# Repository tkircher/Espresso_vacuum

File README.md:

# Espresso vacuum
Released under the Permissive version of the Cern Open Hardware License v2 (CERN-OHL-P)

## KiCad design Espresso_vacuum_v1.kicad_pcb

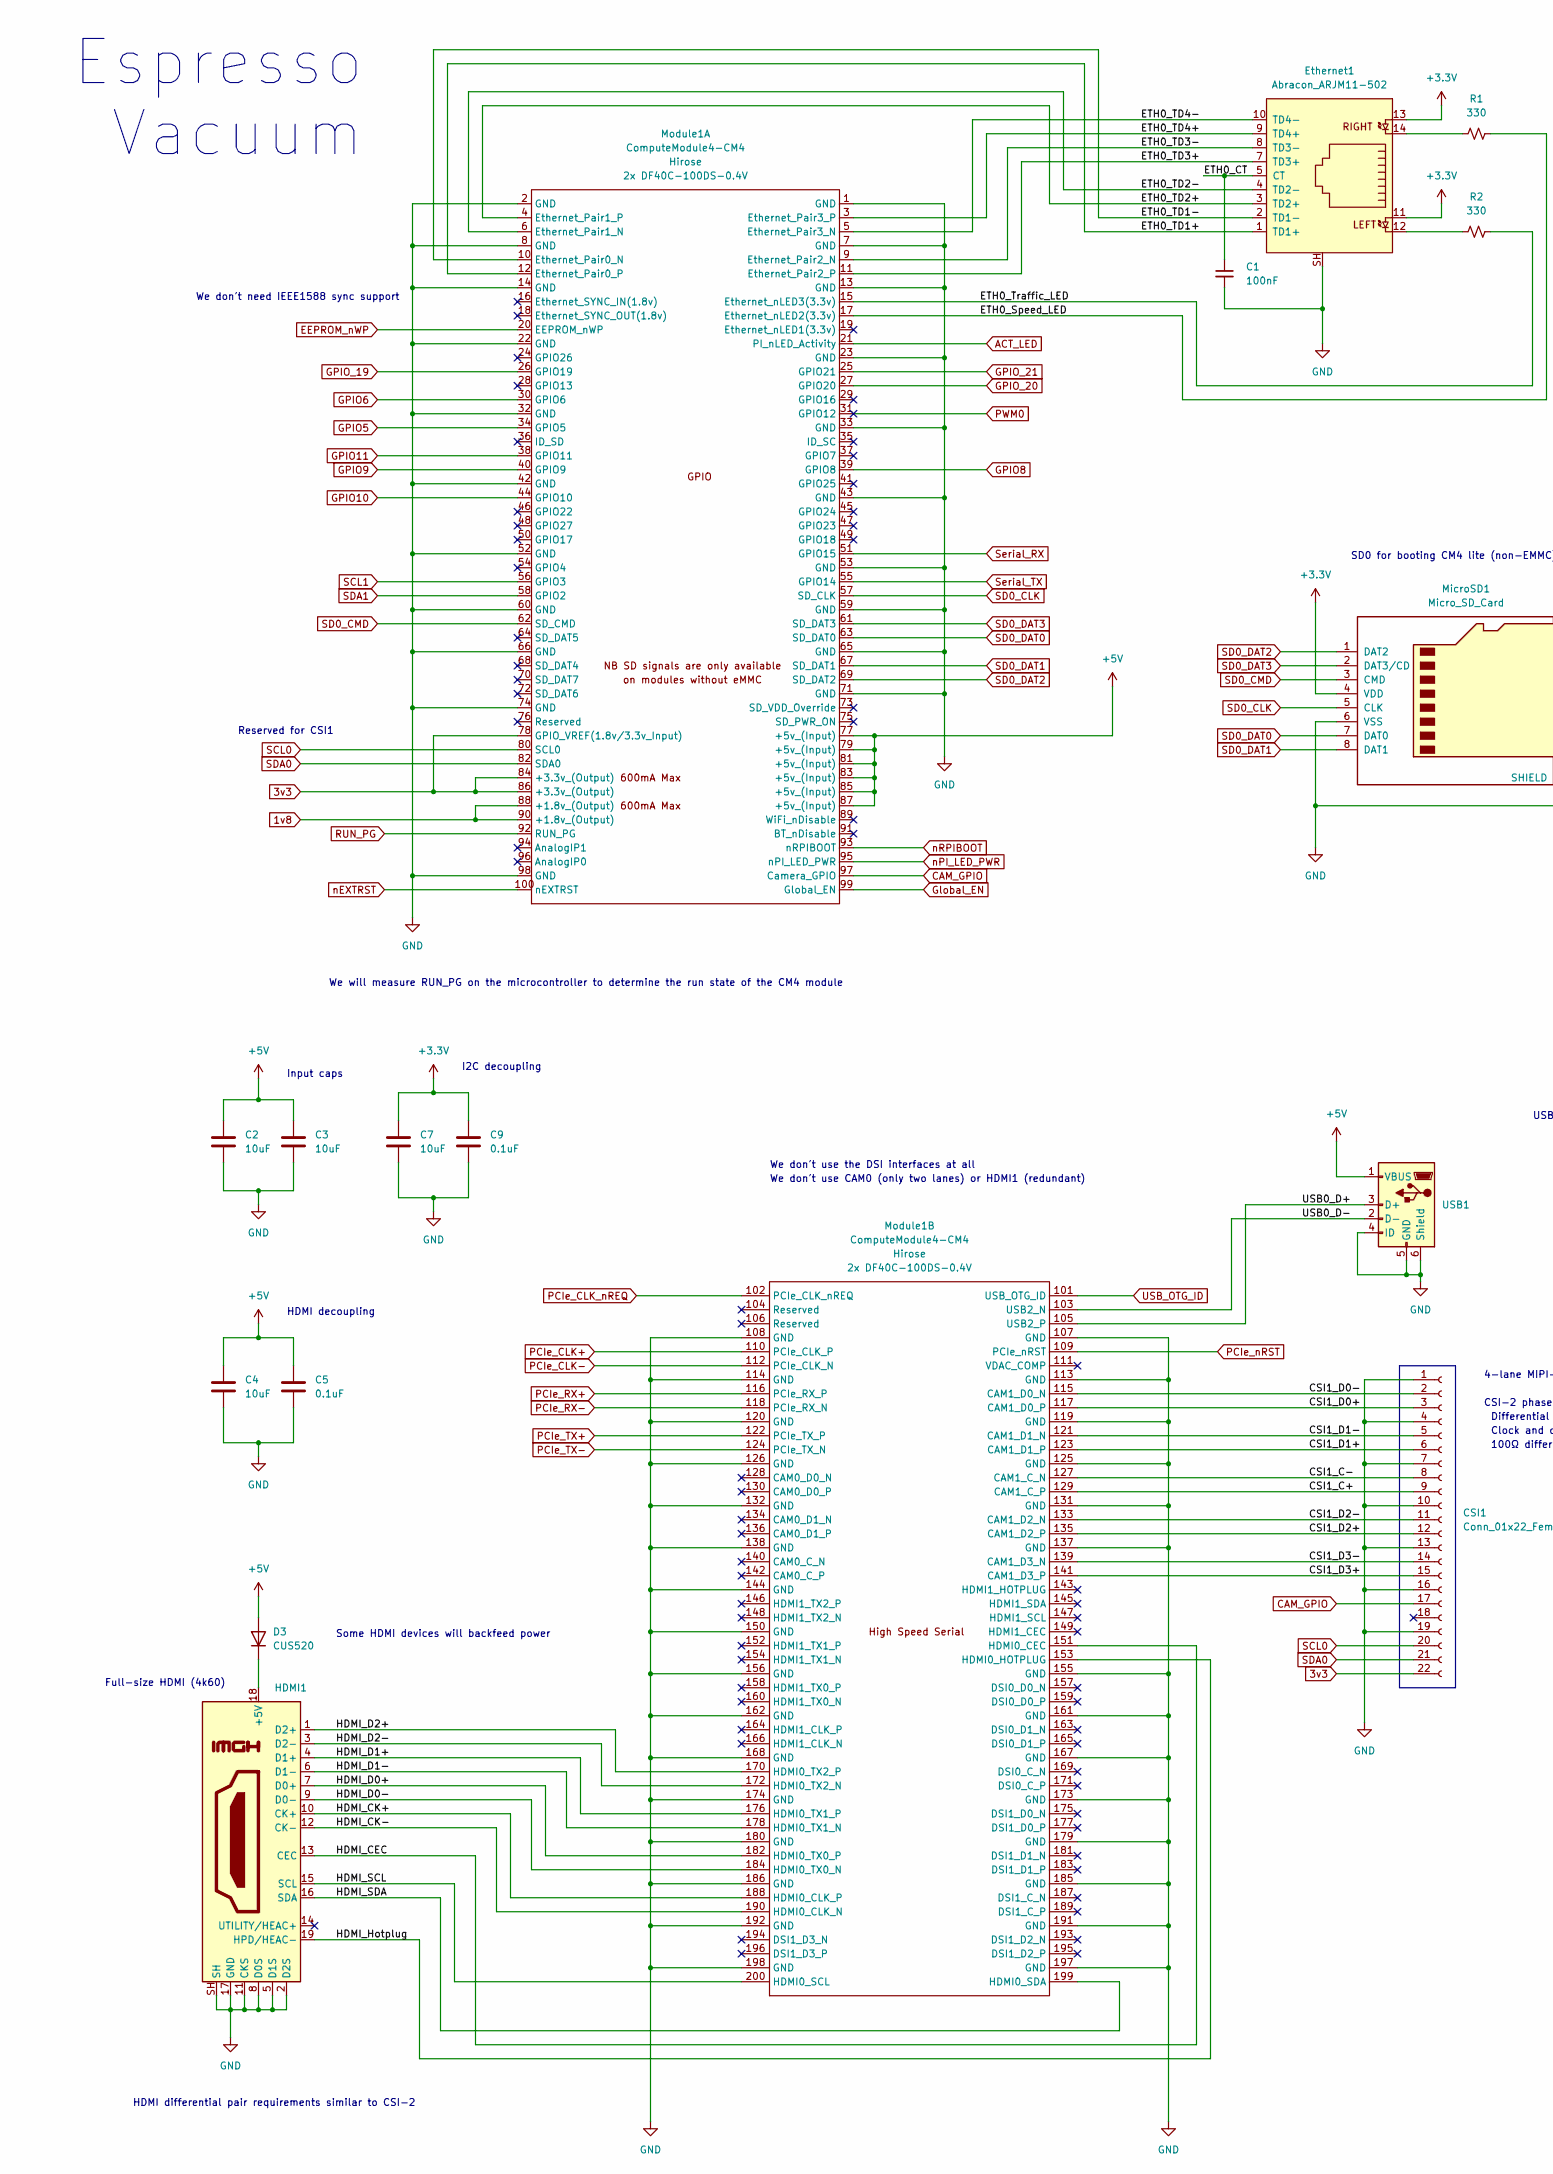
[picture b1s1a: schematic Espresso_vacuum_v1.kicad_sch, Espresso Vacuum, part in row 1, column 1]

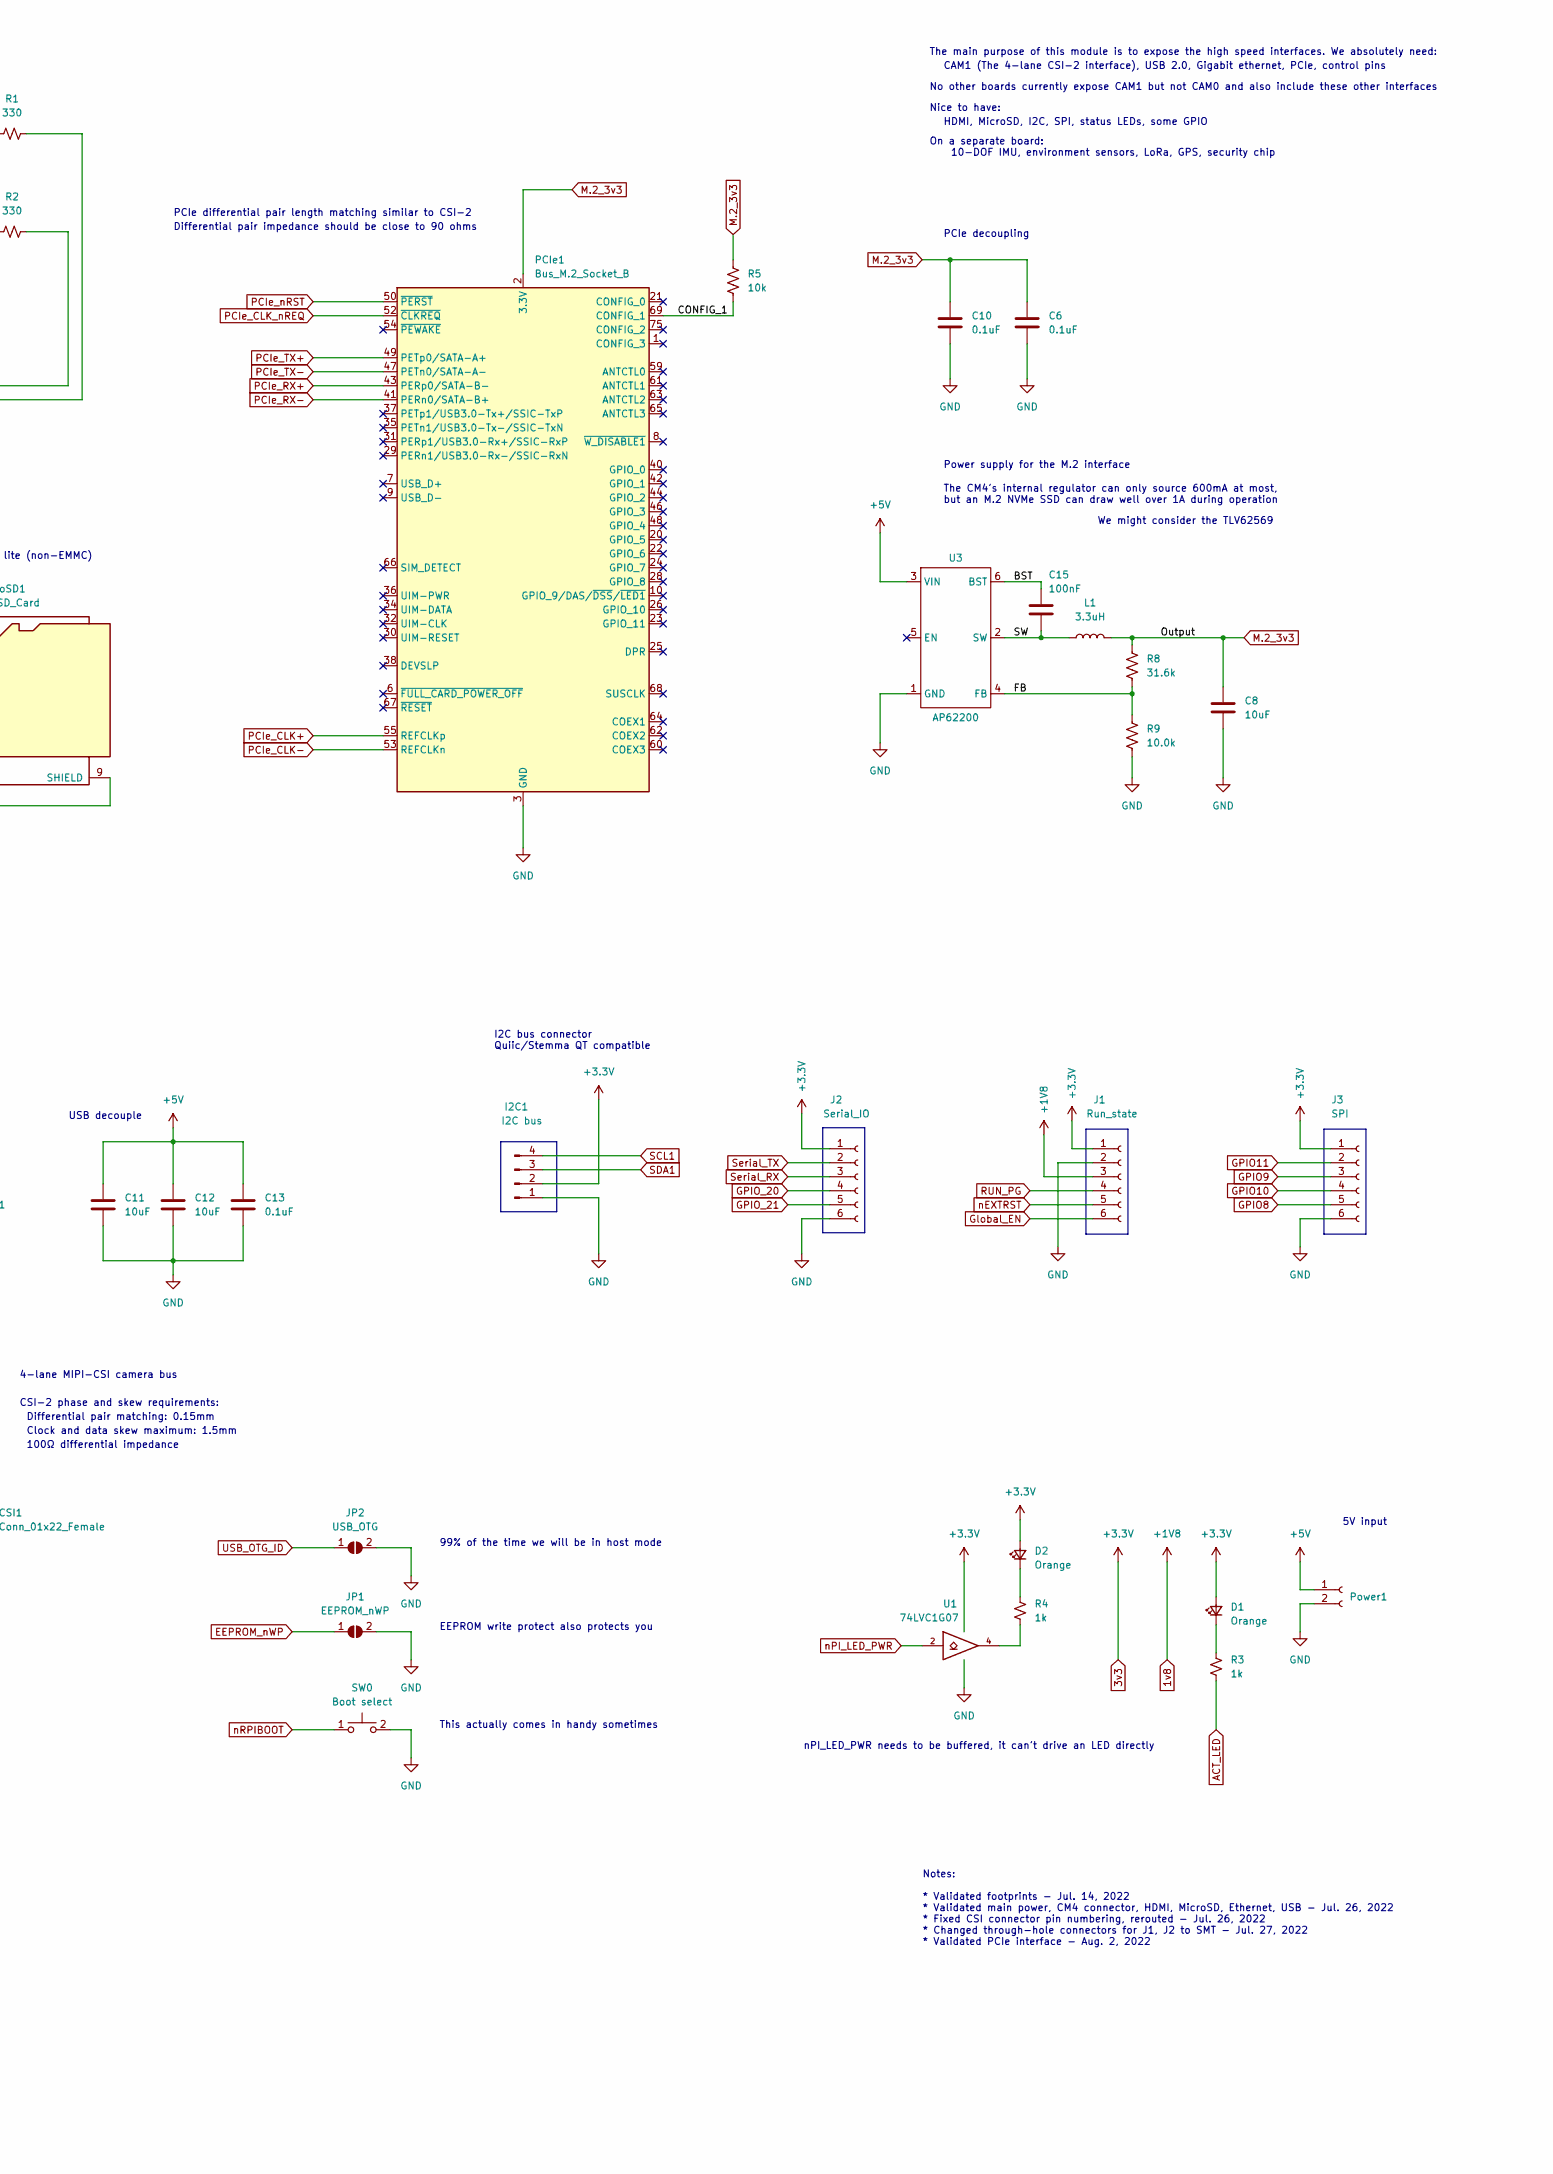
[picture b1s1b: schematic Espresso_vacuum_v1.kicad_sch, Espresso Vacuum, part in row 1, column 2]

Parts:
C1: 100nF; C_0603_1608Metric
C2, C4, C7, C8, C11, C12: 10uF; C_1210_3225Metric
C3: 10uF; CP_EIA-6032-15_Kemet-U
C5, C6, C9, C13: 0.1uF; C_0805_2012Metric
C10: 0.1uF; C_0603_1608Metric
C15: 100nF; C_0805_2012Metric
CSI1: Conn_01x22_Female; Hirose_FH12-22S-0.5SH_1x22-1MP_P0.50mm_Horizontal
D1, D2: Orange; D_0805_2012Metric
D3: CUS520; D_SOD-323
Ethernet1: Abracon_ARJM11-502; RJ45_Abracon_ARJM11
HDMI1: Display_connector; HDMI_A_Molex_208658-1001_Horizontal
I2C1: I2C bus; JST_SH_SM04B-SRSS-TB_1x04-1MP_P1.00mm_Horizontal
J1: Run_state; Molex_Pico-Clasp_202396-0607_1x06-1MP_P1.00mm_Horizontal
J2: Serial_IO; Molex_Pico-Clasp_202396-0607_1x06-1MP_P1.00mm_Horizontal
J3: SPI; Molex_Pico-Clasp_202396-0607_1x06-1MP_P1.00mm_Horizontal
JP1: EEPROM_nWP; SolderJumper-2_P1.3mm_Open_TrianglePad1.0x1.5mm
JP2: USB_OTG; SolderJumper-2_P1.3mm_Open_TrianglePad1.0x1.5mm
L1: 3.3uH; Murata_4040
MicroSD1: Micro_SD_Card; microSD_HC_Hirose_DM3D-SF
Module1: ComputeModule4-CM4; Raspberry-Pi-4-Compute-Module
PCIe1: Bus_M.2_Socket_B; TE_2199119-3
Power1: Conn_01x02_Female; SolderWire-0.75sqmm_1x02_P4.8mm_D1.25mm_OD2.3mm
R1, R2: 330; R_0603_1608Metric
R3, R4: 1k; R_0603_1608Metric
R5: 10k; R_0603_1608Metric
R8: 31.6k; C_0603_1608Metric
R9: 10.0k; C_0603_1608Metric
SW0: Boot select; MJTP1140A
U1: 74LVC1G07; SOT-23-5
U3: AP62200; TSOT-23-6
USB1: microUSB; USB_Micro-B_GCT_USB3076-30-A

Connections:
1v8: J1.3, Module1.88 (+1.8v_(Output)), Module1.90 (+1.8v_(Output))
3v3: C7.1, C9.1, CSI1.22, D1.2 (A), D2.2 (A), Ethernet1.11, Ethernet1.13, I2C1.2, J1.1, J2.1, J3.1, MicroSD1.4 (VDD), Module1.78 (GPIO_VREF(1.8v/3.3v_Input)), Module1.84 (+3.3v_(Output)), Module1.86 (+3.3v_(Output)), U1.5 (VCC)
+5V: C2.1, C3.1, C4.1, C5.1, C11.1, C12.1, C13.1, D3.2 (A), Module1.77 (+5v_(Input)), Module1.79 (+5v_(Input)), Module1.81 (+5v_(Input)), Module1.83 (+5v_(Input)), Module1.85 (+5v_(Input)), Module1.87 (+5v_(Input)), Power1.1, U3.3 (VIN), USB1.1 (VBUS)
/BST: C15.1, U3.6 (BST)
/CONFIG_1: PCIe1.69 (CONFIG_1), R5.2
/CSI1_C+: CSI1.9, Module1.129 (CAM1_C_P)
/CSI1_C-: CSI1.8, Module1.127 (CAM1_C_N)
/CSI1_D0+: CSI1.3, Module1.117 (CAM1_D0_P)
/CSI1_D0-: CSI1.2, Module1.115 (CAM1_D0_N)
/CSI1_D1+: CSI1.6, Module1.123 (CAM1_D1_P)
/CSI1_D1-: CSI1.5, Module1.121 (CAM1_D1_N)
/CSI1_D2+: CSI1.12, Module1.135 (CAM1_D2_P)
/CSI1_D2-: CSI1.11, Module1.133 (CAM1_D2_N)
/CSI1_D3+: CSI1.15, Module1.141 (CAM1_D3_P)
/CSI1_D3-: CSI1.14, Module1.139 (CAM1_D3_N)
/ETH0_CT: C1.1, Ethernet1.5 (CT), Ethernet1.6 (CT)
/ETH0_Speed_LED: Module1.17 (Ethernet_nLED2(3.3v)), R1.1
/ETH0_TD1+: Ethernet1.1 (TD1+), Module1.12 (Ethernet_Pair0_P)
/ETH0_TD1-: Ethernet1.2 (TD1-), Module1.10 (Ethernet_Pair0_N)
/ETH0_TD2+: Ethernet1.3 (TD2+), Module1.4 (Ethernet_Pair1_P)
/ETH0_TD2-: Ethernet1.4 (TD2-), Module1.6 (Ethernet_Pair1_N)
/ETH0_TD3+: Ethernet1.7 (TD3+), Module1.11 (Ethernet_Pair2_P)
/ETH0_TD3-: Ethernet1.8 (TD3-), Module1.9 (Ethernet_Pair2_N)
/ETH0_TD4+: Ethernet1.9 (TD4+), Module1.3 (Ethernet_Pair3_P)
/ETH0_TD4-: Ethernet1.10 (TD4-), Module1.5 (Ethernet_Pair3_N)
/ETH0_Traffic_LED: Module1.15 (Ethernet_nLED3(3.3v)), R2.1
/FB: R8.2, R9.1, U3.4 (FB)
/HDMI_CEC: HDMI1.13 (CEC), Module1.151 (HDMI0_CEC)
/HDMI_CK+: HDMI1.10 (CK+), Module1.188 (HDMI0_CLK_P)
/HDMI_CK-: HDMI1.12 (CK-), Module1.190 (HDMI0_CLK_N)
/HDMI_D0+: HDMI1.7 (D0+), Module1.182 (HDMI0_TX0_P)
/HDMI_D0-: HDMI1.9 (D0-), Module1.184 (HDMI0_TX0_N)
/HDMI_D1+: HDMI1.4 (D1+), Module1.176 (HDMI0_TX1_P)
/HDMI_D1-: HDMI1.6 (D1-), Module1.178 (HDMI0_TX1_N)
/HDMI_D2+: HDMI1.1 (D2+), Module1.170 (HDMI0_TX2_P)
/HDMI_D2-: HDMI1.3 (D2-), Module1.172 (HDMI0_TX2_N)
/HDMI_Hotplug: HDMI1.19 (HPD/HEAC-), Module1.153 (HDMI0_HOTPLUG)
/HDMI_SCL: HDMI1.15 (SCL), Module1.200 (HDMI0_SCL)
/HDMI_SDA: HDMI1.16 (SDA), Module1.199 (HDMI0_SDA)
/SW: C15.2, L1.1, U3.2 (SW)
/USB0_D+: Module1.105 (USB2_P), USB1.3 (D+)
/USB0_D-: Module1.103 (USB2_N), USB1.2 (D-)
ACT_LED: Module1.21 (PI_nLED_Activity), R3.1
CAM_GPIO: CSI1.17, Module1.97 (Camera_GPIO)
EEPROM_nWP: JP1.1 (A), Module1.20 (EEPROM_nWP)
GND: C1.2, C2.2, C3.2, C4.2, C5.2, C6.2, C7.2, C8.2, C9.2, C10.2, C11.2, C12.2, C13.2, CSI1.1, CSI1.4, CSI1.7, CSI1.10, CSI1.13, CSI1.16, CSI1.19, Ethernet1.SH, HDMI1.2 (D2S), HDMI1.5 (D1S), HDMI1.8 (D0S), HDMI1.11 (CKS), HDMI1.17 (GND), HDMI1.SH, I2C1.1, J1.2, J2.6, J3.6, JP1.2 (B), JP2.2 (B), MicroSD1.6 (VSS), MicroSD1.9 (SHIELD), Module1.1 (GND), Module1.2 (GND), Module1.7 (GND), Module1.8 (GND), Module1.13 (GND), Module1.14 (GND), Module1.22 (GND), Module1.23 (GND), Module1.32 (GND), Module1.33 (GND), Module1.42 (GND), Module1.43 (GND), Module1.52 (GND), Module1.53 (GND), Module1.59 (GND), Module1.60 (GND), Module1.65 (GND), Module1.66 (GND), Module1.71 (GND), Module1.74 (GND), Module1.98 (GND), Module1.107 (GND), Module1.108 (GND), Module1.113 (GND), Module1.114 (GND), Module1.119 (GND), Module1.120 (GND), Module1.125 (GND), Module1.126 (GND), Module1.131 (GND), Module1.132 (GND), Module1.137 (GND), Module1.138 (GND), Module1.144 (GND), Module1.150 (GND), Module1.155 (GND), Module1.156 (GND), Module1.161 (GND), Module1.162 (GND), Module1.167 (GND), Module1.168 (GND), Module1.173 (GND), Module1.174 (GND), Module1.179 (GND), Module1.180 (GND), Module1.185 (GND), Module1.186 (GND), Module1.191 (GND), Module1.192 (GND), Module1.197 (GND), Module1.198 (GND), PCIe1.3 (GND), PCIe1.5 (GND), PCIe1.11 (GND), PCIe1.27 (GND), PCIe1.33 (GND), PCIe1.39 (GND), PCIe1.45 (GND), PCIe1.51 (GND), PCIe1.57 (GND), PCIe1.71 (GND), PCIe1.73 (GND), Power1.2, R9.2, SW0.2, U1.3 (GND), U3.1 (GND), USB1.4 (ID), USB1.5 (GND), USB1.6 (Shield)
GPIO5: Module1.34 (GPIO5)
GPIO6: Module1.30 (GPIO6)
GPIO8: J3.5, Module1.39 (GPIO8)
GPIO9: J3.3, Module1.40 (GPIO9)
GPIO10: J3.4, Module1.44 (GPIO10)
GPIO11: J3.2, Module1.38 (GPIO11)
GPIO_19: Module1.26 (GPIO19)
GPIO_20: J2.4, Module1.27 (GPIO20)
GPIO_21: J2.5, Module1.25 (GPIO21)
Global_EN: J1.6, Module1.99 (Global_EN)
M.2_3v3: C6.1, C8.1, C10.1, L1.2, PCIe1.2 (3.3V), PCIe1.4 (3.3V), PCIe1.70 (3.3V), PCIe1.72 (3.3V), PCIe1.74 (3.3V), R5.1, R8.1
unnamed: D1.1 (K), R3.2
unnamed: D2.1 (K), R4.2
unnamed: D3.1 (K), HDMI1.18 (+5V)
unnamed: Ethernet1.12, R2.2
unnamed: Ethernet1.14, R1.2
unnamed: R4.1, U1.4
PCIe_CLK+: Module1.110 (PCIe_CLK_P), PCIe1.55 (REFCLKp)
PCIe_CLK-: Module1.112 (PCIe_CLK_N), PCIe1.53 (REFCLKn)
PCIe_CLK_nREQ: Module1.102 (PCIe_CLK_nREQ), PCIe1.52 (~CLKREQ)
PCIe_RX+: Module1.116 (PCIe_RX_P), PCIe1.43 (PERp0/SATA-B-)
PCIe_RX-: Module1.118 (PCIe_RX_N), PCIe1.41 (PERn0/SATA-B+)
PCIe_TX+: Module1.122 (PCIe_TX_P), PCIe1.49 (PETp0/SATA-A+)
PCIe_TX-: Module1.124 (PCIe_TX_N), PCIe1.47 (PETn0/SATA-A-)
PCIe_nRST: Module1.109 (PCIe_nRST), PCIe1.50 (~PERST)
PWM0: Module1.31 (GPIO12)
RUN_PG: J1.4, Module1.92 (RUN_PG)
SCL0: CSI1.20, Module1.80 (SCL0)
SCL1: I2C1.4, Module1.56 (GPIO3)
SD0_CLK: MicroSD1.5 (CLK), Module1.57 (SD_CLK)
SD0_CMD: MicroSD1.3 (CMD), Module1.62 (SD_CMD)
SD0_DAT0: MicroSD1.7 (DAT0), Module1.63 (SD_DAT0)
SD0_DAT1: MicroSD1.8 (DAT1), Module1.67 (SD_DAT1)
SD0_DAT2: MicroSD1.1 (DAT2), Module1.69 (SD_DAT2)
SD0_DAT3: MicroSD1.2 (DAT3/CD), Module1.61 (SD_DAT3)
SDA0: CSI1.21, Module1.82 (SDA0)
SDA1: I2C1.3, Module1.58 (GPIO2)
Serial_RX: J2.3, Module1.51 (GPIO15)
Serial_TX: J2.2, Module1.55 (GPIO14)
USB_OTG_ID: JP2.1 (A), Module1.101 (USB_OTG_ID)
nEXTRST: J1.5, Module1.100 (nEXTRST)
nPI_LED_PWR: Module1.95 (nPI_LED_PWR), U1.2
nRPIBOOT: Module1.93 (nRPIBOOT), SW0.1

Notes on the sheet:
4-lane MIPI-CSI camera bus
Espresso Vacuum
Differential pair matching: 0.15mm
nPI_LED_PWR needs to be buffered, it can't drive an LED directly
USB decouple
On a separate board: 10-DOF IMU, environment sensors, LoRa, GPS, security chip
HDMI, MicroSD, I2C, SPI, status LEDs, some GPIO
This actually comes in handy sometimes
CAM1 (The 4-lane CSI-2 interface), USB 2.0, Gigabit ethernet, PCIe, control pins
Full-size HDMI (4k60)
100Ω differential impedance
Input caps
Some HDMI devices will backfeed power
HDMI decoupling
No other boards currently expose CAM1 but not CAM0 and also include these other interfaces
CSI-2 phase and skew requirements:
5V input
Differential pair impedance should be close to 90 ohms
Clock and data skew maximum: 1.5mm
HDMI differential pair requirements similar to CSI-2
Reserved for CSI1
I2C decoupling
We will measure RUN_PG on the microcontroller to determine the run state of the CM4 module
PCIe differential pair length matching similar to CSI-2
EEPROM write protect also protects you
99% of the time we will be in host mode
We don't use CAM0 (only two lanes) or HDMI1 (redundant)
I2C bus connector Quiic/Stemma QT compatible
We don't need IEEE1588 sync support
Power supply for the M.2 interface
Nice to have:
PCIe decoupling
The CM4's internal regulator can only source 600mA at most, but an M.2 NVMe SSD can draw well over 1A during operation
The main purpose of this module is to expose the high speed interfaces. We absolutely need:
SD0 for booting CM4 lite (non-EMMC)
We might consider the TLV62569
We don't use the DSI interfaces at all
Notes: * Validated footprints - Jul. 14, 2022 * Validated main power, CM4 connector, HDMI, MicroSD, Ethernet, USB - Jul. 26, 2022 * Fixed CSI connector pin numbering, rerouted - Jul. 26, 2022 * Changed through-hole connectors for J1, J2 to SMT - Jul. 27, 2022 * Validated PCIe interface - Aug. 2, 20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

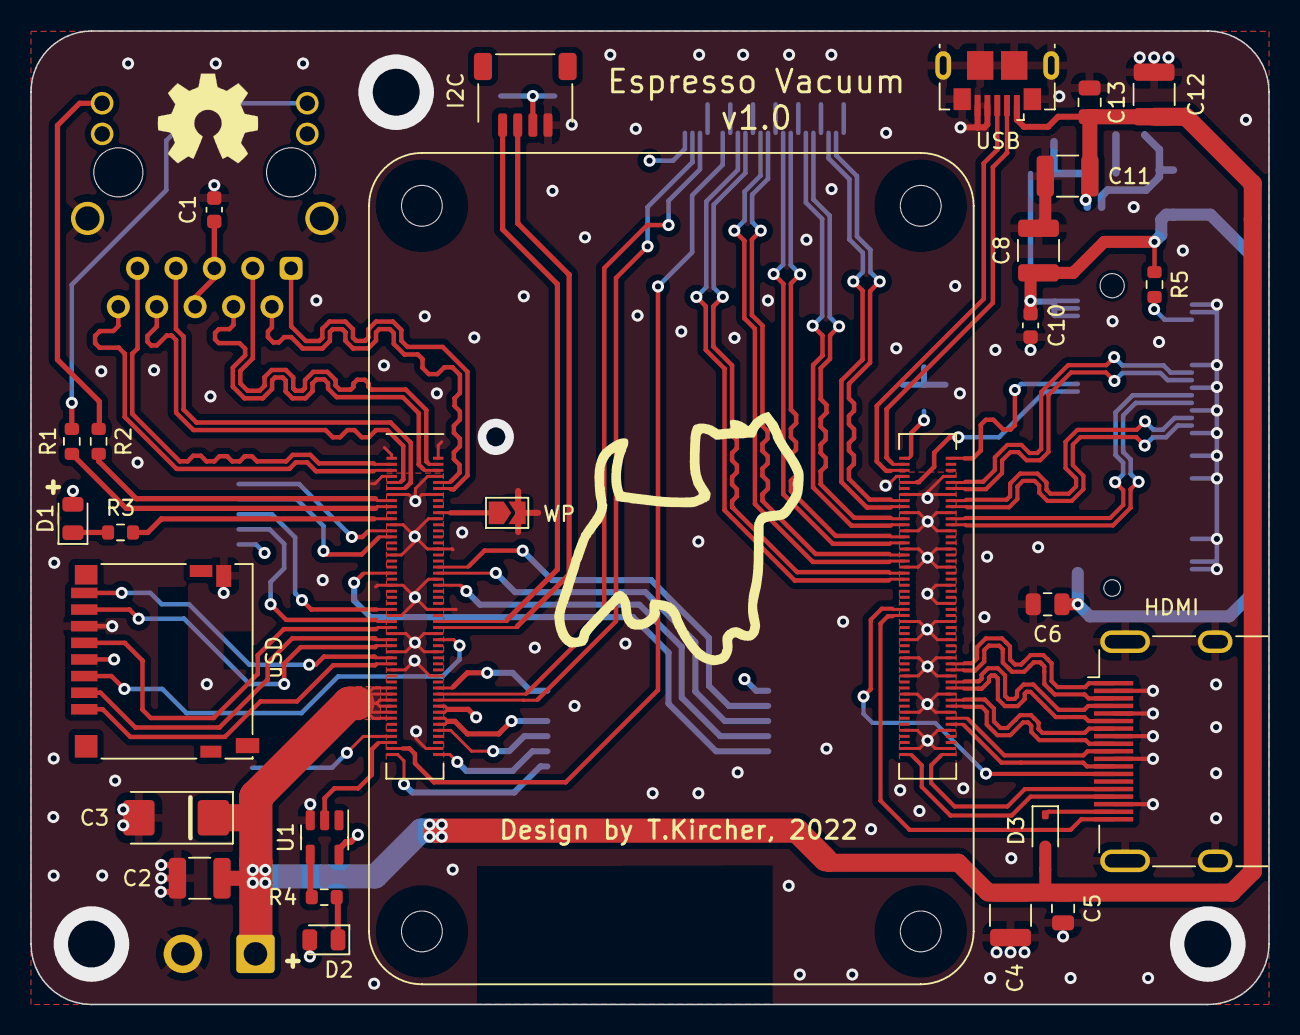
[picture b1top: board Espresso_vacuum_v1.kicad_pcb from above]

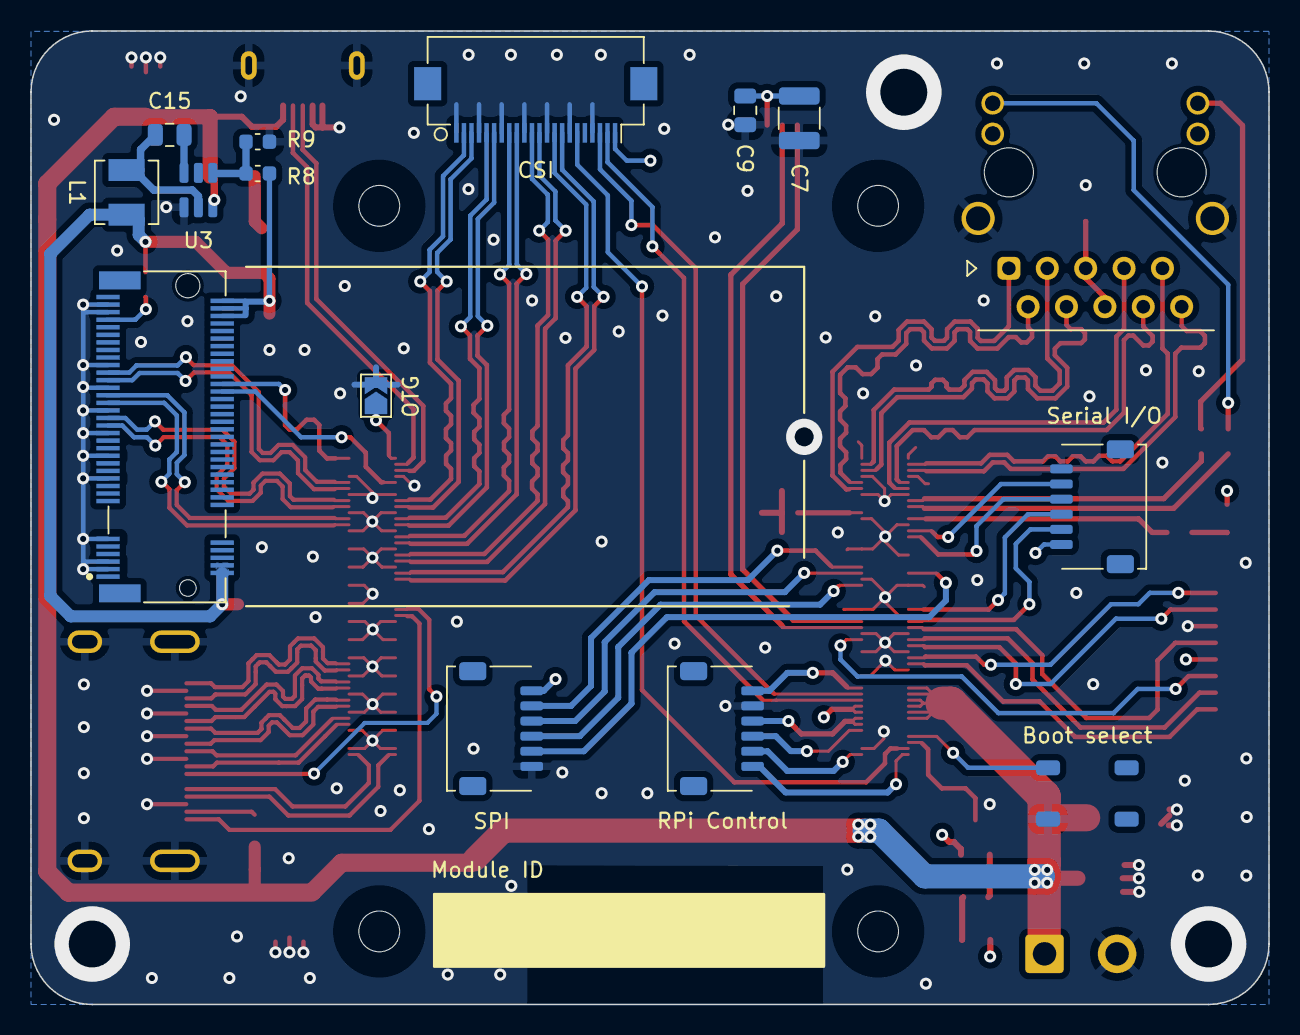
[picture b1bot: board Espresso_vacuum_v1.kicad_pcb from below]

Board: 4 copper layers, 81.9 x 64.4 mm, 42 parts (15 on the bottom side), 85 nets.

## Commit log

2023-04-29 Add files via upload
    Initial upload
2023-04-30 Added board render
2025-01-06 Create LICENSE
